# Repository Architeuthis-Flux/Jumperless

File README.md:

# Jumperless
### a jumperless breadboard

##### If you want one of these, they're available in [my Tindie store](https://www.tindie.com/products/architeuthisflux/jumperless/)

# There's now a way cooler version, [Jumperless V5](https://github.com/Architeuthis-Flux/JumperlessV5) 

#### You can get a V5 [on Crowd Supply](https://www.crowdsupply.com/architeuthis-flux/jumperless-v5)

## [Getting started using your Jumperless](https://hackaday.io/project/191238-jumperless/log/222858-getting-started-using-your-jumperless)
###### (at this point some of the stuff in that guide is a bit out of date, but generally is good advice)

(You can click on this to watch the explainer video)

Using a bunch of analog crosspoint switches wired together into one bigger switch, this breadboard makes real, hardware connections between any points on the board or the Arduino Nano header at the top via software command, instead of needing to use jumper wires.

#### [3D Printable Stand](https://www.printables.com/model/684090-stand-for-the-jumperless-breadboard) (you can drop the model through the build plate to adjust the height)

#### [3D Printable Jumperless Trap](https://www.printables.com/model/1040448-jumperless-v1-3-case) (jk it's a carrying case, but make sure you can get it back open before you put your Jumperless in it)

Try this Wokwi project if something isn't working: https://wokwi.com/projects/389569655762010113

Here's an example of me using this thing to connect some I2C pins from an Arduino to an OLED

https://github.com/Architeuthis-Flux/Jumperless/assets/20519442/0da0fdcb-c629-4f16-8638-6fab5f5c69fc

Jumperless also has a ton of voltage/current sensing so the RGB LEDs underneath each row can show a ton of information about what's going on with your circuit. 2 buffered high-current DACs (one 0-5V and one ±8V), 4 buffered and level-shifted 12-bit ADCs (3 are 0-5V and 1 for ±8V), 2 INA219 current and voltage measurement ICs, and 4 GPIO to simulate digital or analog signals that can be routed to anywhere on the breadboard or the Arduino Nano header.

https://github.com/Architeuthis-Flux/Jumperless/assets/20519442/e701d5c8-2349-49a1-8d57-8574962e7c29

Use it to probe the pins on an unknown IC (which is what I'm doing in the video above), or for some automated fuzzing, or to help guide you through converting a schematic to a real circuit, or do whatever the hell you want with it. 

The connections are real and fully analog (-8V to +8V, up to around 1 MHz before signal quality starts to degrade) instead of cheating with some measure-then-simulate setup, although you can do that too if you want to simulate a [memristor](https://en.wikipedia.org/wiki/Memristor) or to send jumpers over the internet.

https://github.com/Architeuthis-Flux/Jumperless/assets/20519442/2c203686-e02e-4a0c-b5eb-0cab925386fb

### If you want to read about how the code and stuff works, [the README in JumperlessNano](https://github.com/Architeuthis-Flux/Jumperless/tree/main/JumperlessNano) goes through how each part works in more detail.

### Or check out the [Hackaday.io page](https://hackaday.io/project/191238-jumperless) and the [Hackaday Blog Writeup](https://hackaday.com/2023/08/25/hackaday-prize-2023-jumperless-the-jumperless-jumperboard/)

And no, it's not an FPGA.

Here it is running a 555 circuit (note that this is a Rev 1 without the through-PCB LEDs)

https://github.com/Architeuthis-Flux/Jumperless/assets/20519442/9c5d2b5a-3727-4197-b1d0-bd45b5f95559

Here are some fun bonus shots

https://github.com/Architeuthis-Flux/Jumperless/assets/20519442/b933e817-c6e4-4d97-9fc0-7b8d9e875ebb
[SchematicRevision3.pdf](https://github.com/Architeuthis-Flux/Jumperless/files/12603152/SchematicRevision3.pdf)

https://github.com/Architeuthis-Flux/Jumperless/assets/20519442/d070d99d-b6b3-43e3-adee-4ca2d7358a9a

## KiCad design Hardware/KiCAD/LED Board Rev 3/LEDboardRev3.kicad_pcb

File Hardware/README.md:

# Jumperless Kit Assembly Instructions

If you get a Jumperless Kit (or order your own boards with SMD parts assembled)
The assembly is pretty easy, it's all through hole stuff.

Here's a montage of all the steps to give an overview of what you'll be doing

https://github.com/Architeuthis-Flux/Jumperless/assets/20519442/656154ef-31c5-4099-a5ea-eef67134b63d

If you've gone through the trouble of ordering your own boards and everything, I'd be happy to send you a free set of spring clips, which is the only part with a huge minimum order quantity and having them made was a whole thing.

Your kit will come in ~7 parts:

- Main board (all the SMD stuff assembled)
- LED “wishbone” board (the LEDs around the header that shine through the board)
- 2 x 15 pin female headers
- Plastic breadboard shell (I’ll include white and black so you can choose)
- 80 x breadboard spring clips
- 1 x LT1054 in 8 pin DIP
- 4 x Sticky-backed rubber feet

- Carefully snap of the edge rails from the LED wishbone board. Put the V-cut on the edge of a table and slowly bend it until it breaks off. 

- Use the 300 grit sandpaper lightly on the tops of the LEDs on the main board to diffuse the light a bit, you don't need to do this on the reverse-mounted "wishbone" board. You can use masking tape so you don't accidentally sand the board for aesthetic reasons (but there are very few traces on the top layer and you shouldn't be sanding hard enough to break a trace.)

When you're finished the LEDs should look like this (before is on the left)

- Put the spring clips into the breadboard shell first and make sure they're all pushed all the way in. Then gently put that onto the main PCB, it may take some careful wiggling to coax all the tabs on the spring clips to go into their holes. If you can't get it seated, take it off and check that they're all straight and in a nice row. If some are giving you trouble, bend it back or swap it out (I have included extras.)

- Stick pin headers into every row of the breadboard and leave them in for soldering. Put them in one hole from the center hole. This makes sure that all the clips are perfectly aligned.

- Solder all the clips, it works best to use a large soldering iron tip and start from the middle on each row. The breadboard will expand slightly as it gets warm so I try to account for that by making sure it expands evenly from the center.

- Place the LT1054 into the footprint between the headers, on the front side of the board. Pin 1 is the bottom left (the square pad) so the notch on the chip should be towards the big yellow capacitors.

- Stick an Arduino Nano in the top headers while you solder them so they stay straight, before doing anything with the wishbone LED board. And wiggle it around to find the nicest looking position (the holes are slightly bigger than the pins so you can wiggle it ~0.5mm) if you're a total perfectionist like me. Then solder it in.

- You'll want to clean off the flux before you put on the wishbone board so there isn't any flux between the LEDs and the PCB. I like to shatter it all by dragging pokey tweezers over it, brush it off, and then use alcohol swabs or MG Chemicals Super Wash spray (this stuff is an absolute game changer, I recommend getting a can)

- For the wishbone board, solder the 2 inner ground pins directly to the backside of the female header pins that are sticking through. Make sure the LEDs lay flat to the main board.

- Stick the 3 other header pins through the wishbone board just far enough that they're flush on the top of the main board. If you stick the short side of the header pin up to the plastic, it turns out that is the perfect length. Tape the headers down so they don't fall out when you flip the board. Solder from the front of the main board first so it's just a flat spot of solder. Now cut the header pins flush before soldering. None of this is strictly necessary, but it leaves the board looking really nice instead of having soldered-then-cut poky headers.

- Clean off all the flux like you did above.

- Peel and stick the rubber feet, 2 on the bottom, 1 by the GPIO headers, and 1 just under the logo on the back. If it's a bit wobbly, a small amount of heat will soften the one giving you issues, then press it onto a flat surface until the wobbliness is gone.

- You can load the firmware by plugging it in with the USB Boot button held and dragging the .uf2 file from here into the drive that pops up as RPI-RP2

And your Jumperless should be good to go!

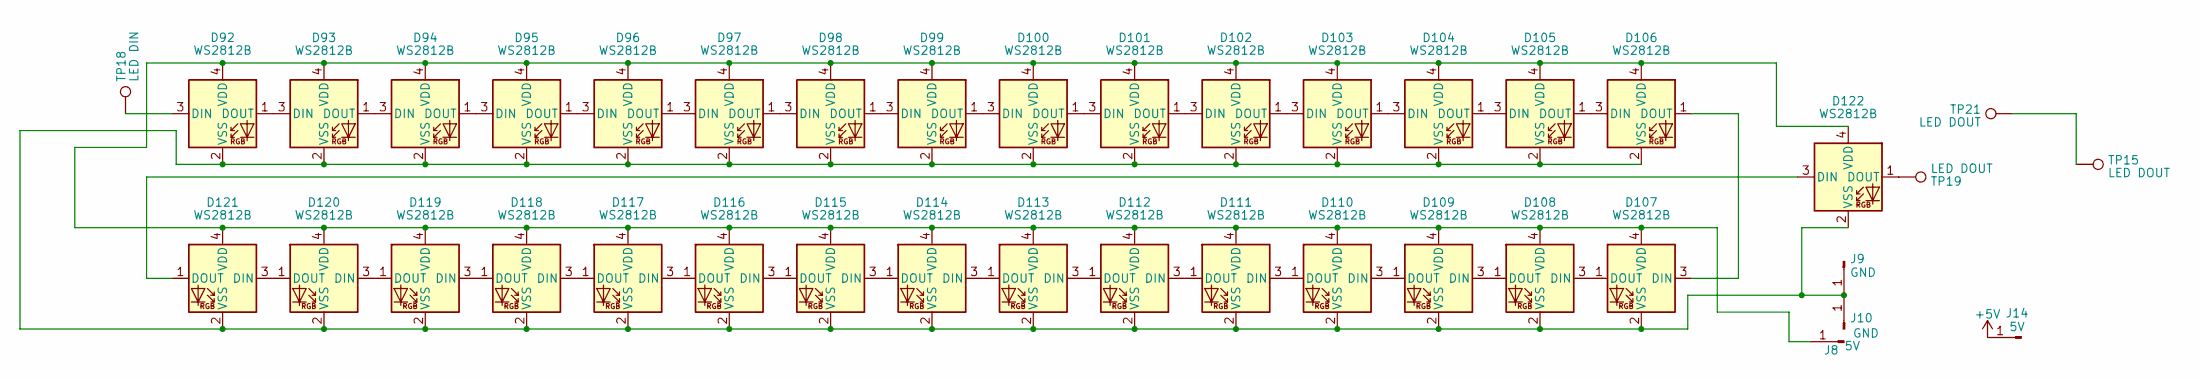
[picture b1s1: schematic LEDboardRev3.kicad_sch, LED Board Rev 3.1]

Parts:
D92, D93, D94, D95, D96, D97, D98, D99, D100, D101, D102, D103, D104, D105, D106, D107, D108, D109, D110, D111, D112, D113, D114, D115, D116, D117, D118, D119, D120, D121, D122: WS2812B; ws2812c-2020-noSolk
J8, J14: 5V; PINHEADER-1x1_vertical
J9, J10: GND; PINHEADER-1x1_vertical
TP15: LED DOUT; TestPoint_Pad_D1.0mm
TP18: LED DIN; PINHEADER-1x1_vertical
TP19, TP21: LED DOUT; PINHEADER-1x1_vertical

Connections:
unnamed: D92.3 (DIN), TP18.1
unnamed: D92.1 (DOUT), D93.3 (DIN)
unnamed: D93.1 (DOUT), D94.3 (DIN)
unnamed: D94.1 (DOUT), D95.3 (DIN)
unnamed: D95.1 (DOUT), D96.3 (DIN)
unnamed: D96.1 (DOUT), D97.3 (DIN)
unnamed: D97.1 (DOUT), D98.3 (DIN)
unnamed: D98.1 (DOUT), D99.3 (DIN)
unnamed: D99.1 (DOUT), D100.3 (DIN)
unnamed: D100.1 (DOUT), D101.3 (DIN)
unnamed: D92.4 (VDD), D93.4 (VDD), D94.4 (VDD), D95.4 (VDD), D96.4 (VDD), D97.4 (VDD), D98.4 (VDD), D99.4 (VDD), D100.4 (VDD), D101.4 (VDD), D102.4 (VDD), D103.4 (VDD), D104.4 (VDD), D105.4 (VDD), D106.4 (VDD), D107.4 (VDD), D108.4 (VDD), D109.4 (VDD), D110.4 (VDD), D111.4 (VDD), D112.4 (VDD), D113.4 (VDD), D114.4 (VDD), D115.4 (VDD), D116.4 (VDD), D117.4 (VDD), D118.4 (VDD), D119.4 (VDD), D120.4 (VDD), D121.4 (VDD), D122.4 (VDD), J8.1
unnamed: D92.2 (VSS), D93.2 (VSS), D94.2 (VSS), D95.2 (VSS), D96.2 (VSS), D97.2 (VSS), D98.2 (VSS), D99.2 (VSS), D100.2 (VSS), D101.2 (VSS), D102.2 (VSS), D103.2 (VSS), D104.2 (VSS), D105.2 (VSS), D106.2 (VSS), D107.2 (VSS), D108.2 (VSS), D109.2 (VSS), D110.2 (VSS), D111.2 (VSS), D112.2 (VSS), D113.2 (VSS), D114.2 (VSS), D115.2 (VSS), D116.2 (VSS), D117.2 (VSS), D118.2 (VSS), D119.2 (VSS), D120.2 (VSS), D121.2 (VSS), D122.2 (VSS), J9.1, J10.1
unnamed: D101.1 (DOUT), D102.3 (DIN)
unnamed: D102.1 (DOUT), D103.3 (DIN)
unnamed: D103.1 (DOUT), D104.3 (DIN)
unnamed: D104.1 (DOUT), D105.3 (DIN)
unnamed: D105.1 (DOUT), D106.3 (DIN)
unnamed: D106.1 (DOUT), D107.3 (DIN)
unnamed: D107.1 (DOUT), D108.3 (DIN)
unnamed: D108.1 (DOUT), D109.3 (DIN)
unnamed: D109.1 (DOUT), D110.3 (DIN)
unnamed: D110.1 (DOUT), D111.3 (DIN)
unnamed: D111.1 (DOUT), D112.3 (DIN)
unnamed: D112.1 (DOUT), D113.3 (DIN)
unnamed: D113.1 (DOUT), D114.3 (DIN)
unnamed: D114.1 (DOUT), D115.3 (DIN)
unnamed: D115.1 (DOUT), D116.3 (DIN)
unnamed: D116.1 (DOUT), D117.3 (DIN)
unnamed: D117.1 (DOUT), D118.3 (DIN)
unnamed: D118.1 (DOUT), D119.3 (DIN)
unnamed: D119.1 (DOUT), D120.3 (DIN)
unnamed: D120.1 (DOUT), D121.3 (DIN)
unnamed: D121.1 (DOUT), D122.3 (DIN)
unnamed: D122.1 (DOUT), TP19.1
unnamed: TP15.1, TP21.1

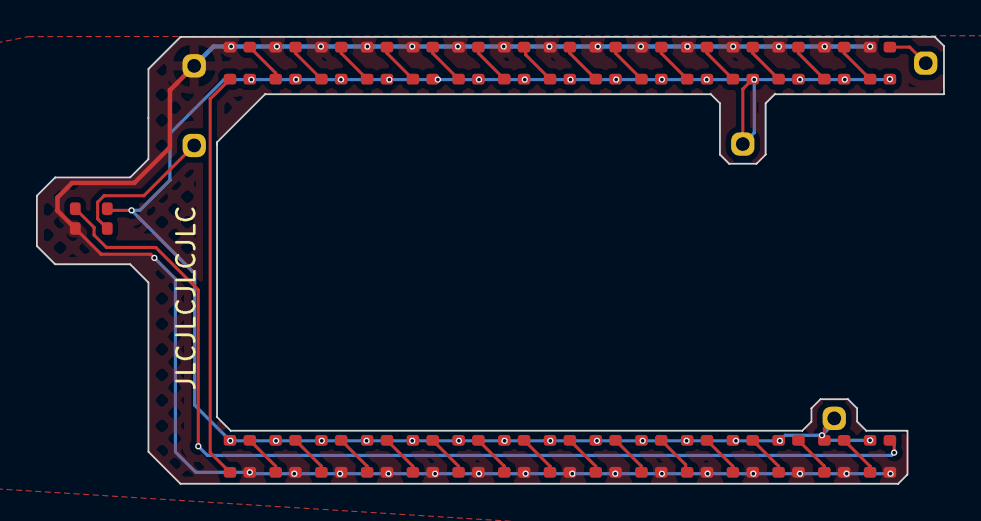
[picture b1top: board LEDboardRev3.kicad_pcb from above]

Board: 2 copper layers, 50.4 x 24.8 mm, 36 parts (0 on the bottom side), 34 nets.

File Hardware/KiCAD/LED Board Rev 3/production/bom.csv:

Designator,Footprint,Quantity,Value,LCSC Part #
"D100, D101, D102, D103, D104, D105, D106, D107, D108, D109, D110, D111, D112, D113, D114, D115, D116, D117, D118, D119, D120, D121, D122, D92, D93, D94, D95, D96, D97, D98, D99",ws2812c-2020-noSolk,31,WS2812B,
"J10, J9",PINHEADER-1x1_vertical,2,GND,
J8,PINHEADER-1x1_vertical,1,5V,
TP18,PINHEADER-1x1_vertical,1,LED IN,
TP19,PINHEADER-1x1_vertical,1,LED OUT,

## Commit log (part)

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2023-03-25 Create f
2023-03-25 Create e
2023-03-25 Create d
2023-03-25 Create c
2023-05-25 New Hardware revision
2023-05-25 Get outta here, .DS_store
2023-05-25 Removed...
2023-05-25 fuck you .DS_Store
2023-05-25 seriously
2023-05-27 Added a bunch of stuff, mainly dealing with nets
2023-05-29 uploading nets from a file works now
2023-05-29 Create README.md for code
2023-05-31 started pathfinding logic
2023-05-31 LED stuff
2023-06-04 chippin' away at shit
2023-06-04 thinking about talking to the DACS
2023-06-05 almost there with the pathfinding stuff
2023-06-06 pathfinding almost works
2023-06-07 do they make micorocontrollers with quibits?
2023-06-07 paths finally work!
2023-06-09 it finally jumps!
    added some PIO assembly to talk to the ch446qs
2023-06-14 now you can load wokwi diagram files
2023-06-24 Bridge app now auto updates
2023-06-24 New Hardware
2023-06-25 arduino stuff
2023-06-26 added ifdefs so Eric can find out why his isnt working
2023-06-26 debugflags update
2023-07-02 DACs and bridge App
2023-07-02 bridge mistake
2023-07-05 Upgraded Wokwi bridge
    The new bridge app passes the serial data through to the terminal window
2023-07-05 fixin bullshit
2023-07-05 New Wokwi Bridge App
2023-07-08 now running led stuff on core 2, and autodetection of ports
2023-07-20 fixed a few little things
2023-07-20 Updated Bridge app
2023-07-30 Update LICENSE
2023-08-06 LED brightness menu and more hardware files
2023-08-06 cleanup
2023-08-12 Rev 3 DAC updates
2023-08-15 Fixed a routing Bug
    it wasn't making certain hop connections, should be fixed now
2023-08-25 Update README.md
    Pathfinding section
2023-08-28 Fixed rev 2 support
2023-08-30 Update README.md with how I control the CH446Qs
2023-09-06 Added LED testing menu
2023-09-06 fix LED menus a bit
2023-09-06 Add Tester Firmware
2023-09-19 Fixed a bug where bounces wouldn't check for overlaps
    phew
2023-09-27 Fixed brightness menu
    removed annoying warnings
2023-10-28 Fixed routing for Special Function chips
2023-10-31 Keep on fixin' shit
2023-11-16 Adjusting timing and delays to make things feel a bit snappier
2023-12-04 Create Packaging folder
2023-12-04 Add Packaging files
2023-12-06 Added Voltage/Current sensing interface
    toggle it on with 'v' in the main menu. You'll need the new Wokwi bridge app to connect the current sensor lines
2023-12-06 Updated bridge app to work with windows better
2023-12-08 Holy shit, routable USB-Serial is working
2023-12-15 Fixed define collision with tusb_common.h so you won't need to edit the library
2023-12-15 Now the connections can be received from UART
2023-12-16 UART control polishing
2023-12-16 fixed parsing and arduino control
2023-12-18 fixed an edge case routing bug
2023-12-22 test universal app
2023-12-31 Added Machine command parsing
2023-12-31 Fix build on case-sensitive filesystem
2023-12-31 testing VScode Source Control fuckery
2023-12-31 Accepts ::lightnet for +-8V and header glow and stuff
2024-01-01 Add machine commands "getnetlist", "getbridgelist"
    - `::getnetlist[]`: prints the in a machine-readable way
    ```
    ::netlist-begin
    ::net[1,1,GND,true,001c04,false,GND]
    ::net[2,2,5V,true,1c0702,false,+5V]
    ::net[3,3,3V3,true,1c0107,false,+3.3V]
2024-01-01 Remove a silly thing I added for testing
2024-01-02 Added an svg interactive Jumperless for people who want to use it to make web apps or whatever
2024-01-03 Machine mode: respond to commands to signal success
    After processing a machine-mode instruction, respond with "::ok\r\n".
    This way the host side knows if an instruction was processed or not.
    Also instructions can carry an optional "sequence number" now, which
    will be echoed in the "ok" response.
    Example:
    ::lightnode:23[...]
2024-01-03 machine mode wasn't parsing the first node
2024-01-03 machine mode fixes
2024-01-03 left in a print
2024-01-04 || should've been &&
2024-01-06 machine-mode: getsupplyswitch
    Example:
    SEND ::getsupplyswitch:1395[]
    REVC ::supplyswitch[5V]
    REVC ::ok:1395
2024-01-10 Accept `#` prefix for colors
2024-01-12 Added brightness scaling so it doesn't melt when using Jumperlab
2024-01-12 Scale down brightness to work with Jumperlab
2024-01-12 Added USB-Serial baud rate selection
2024-01-12 Add "load last net" if connected to a power bank with no USB host
2024-01-13 allow you to load last nets even when connected to a host
2024-01-15 Fixed a bunch of routing bugs
2024-01-28 Add SPDX-License-Identifier to JumperlessNano/src/ files
2024-01-28 Add SPDX-License-Idnetifier to JumperlessWokwiBridge
2024-01-28 Create z
2024-01-28 Added all the production files
2024-01-29 Add Schematic with OSHW licenses
2024-02-01 check other side of hops
2024-02-01 Fixed delays so things run quicker and don't drop incoming characters
2024-02-01 Deleting a bunch of crap
2024-02-03 add canonical defines and an option to print the long or short versions
2024-02-09 Add command 'getchipstatus'
2024-02-12 Create Roadmap.md
    Feel free to PR this with new things you want to add
2024-02-13 Probing almost works for now it just prints what it touched. Added scaling up for Jumperlab.
2024-02-13 I have no idea
2024-02-13 Added early probing support
2024-02-14 Added probing!!!
2024-02-14 Probing mode improvements
2024-02-15 Continously sample ADCs and expose them via USB HID
2024-02-16 Add copy of Adafruit_TinyUSB_Arduino library
2024-02-16 Add custom class driver, instead of using HID
2024-02-16 Use adcReadings instead of analogRead
2024-02-16 Probing is it's own file and works on the nano header, fixed routing bugs, keep track of unconnected paths
2024-02-16 Fucking versioning
2024-02-16 machine command tweak
2024-02-18 rewrote probing
2024-02-18 probe
2024-02-18 tiny tweaks to probing
2024-02-19 Better probing menu, disambuguation of shorted rows, add a flag to swap probe/button pins
2024-02-19 add a double button press timer
2024-02-20 Fix node file clear and restore, make disambiguation a different color
2024-02-20 Add voltage selection to probing, more colors on status led
2024-02-24 Added footpint and font files, took out spaces from folder names
2024-02-24 Removed a file I stupidly put a slash in the name of
2024-02-24 Got another sloush
2024-02-24 Create Windows Folder
2024-02-24 Put up windows stuff
2024-02-25 Remove backups so the repo is less huge
2024-03-04 Slowed down sending data to chips
2024-03-06 Pulldown button pin so you can put an LED on the probe
2024-03-14 Added KiCAD and Producion Files for Rev3.1
2024-05-27 Added Rotary Encoder Mode and multiple saved slots
2024-05-28 Added contact info and stuff to be super duper open source
2024-06-19 I broke something in the last release, this should fix it
2024-11-11 Made last connections load on startup
2024-11-17 added the beginnings of an address incrementer function
2024-11-21 The janky example address incrementer doesn't clear between addresses
2024-11-22 fixed not clearing connections between Wokwi updates
2024-12-01 added a super-duper raw xy command and a way to toggle GPIO_0
2025-02-11 dont use any of this
2025-02-12 Added 'ack' to recieving connections from arduino (see examples), Allow you to just read the probe with 'j'
2025-02-12 update version number
